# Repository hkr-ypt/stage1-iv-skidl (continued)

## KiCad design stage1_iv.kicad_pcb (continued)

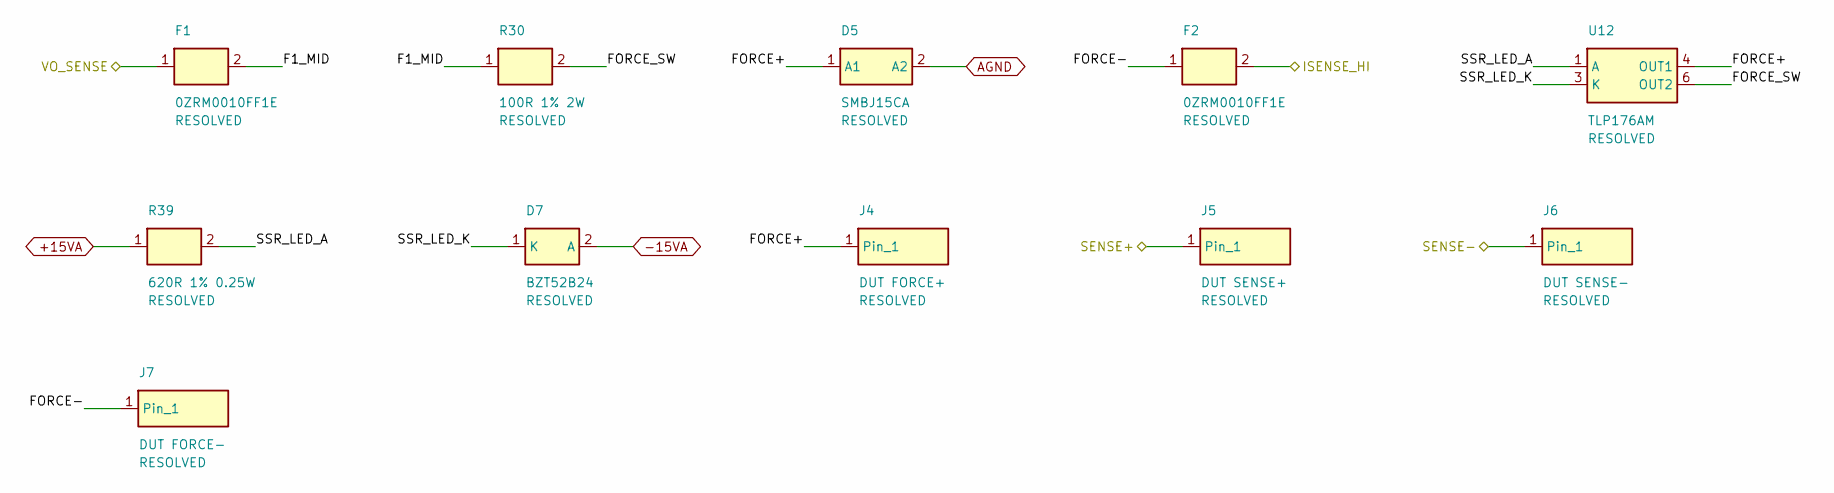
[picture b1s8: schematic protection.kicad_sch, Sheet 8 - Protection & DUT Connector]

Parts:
D5: SMBJ15CA; D_SMB; MPN SMBJ15CA
D7: BZT52B24; D_SOD-123; MPN BZT52B24-E3-08
F1, F2: 0ZRM0010FF1E; Fuse_Bourns_MF-RG300; MPN 0ZRM0010FF1E
J4: DUT FORCE+; Banana_Jack_1Pin; MPN panel-mount-banana-4mm
J5: DUT SENSE+; Banana_Jack_1Pin; MPN panel-mount-banana-4mm
J6: DUT SENSE-; Banana_Jack_1Pin; MPN panel-mount-banana-4mm
J7: DUT FORCE-; Banana_Jack_1Pin; MPN panel-mount-banana-4mm
R30: 100R 1% 2W; R_Axial_DIN0411_L9.9mm_D3.6mm_P12.70mm_Horizontal; MPN PR02000201000FA100
R39: 620R 1% 0.25W; R_1206_3216Metric; MPN generic
U12: TLP176AM; Toshiba_SOIC-4-6_4.4x3.6mm_P1.27mm; MPN TLP176AM(TPL,E

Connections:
+15VA: R39.1; also elsewhere on the board
-15VA: D7.2 (A); also elsewhere on the board
/ISENSE_HI: F2.2; also elsewhere on the board
/SENSE+: J5.1; also elsewhere on the board
/SENSE-: J6.1; also elsewhere on the board
/VO_SENSE: F1.1; also elsewhere on the board
/protection/F1_MID: F1.2, R30.1
/protection/FORCE+: D5.1 (A1), J4.1, U12.4 (OUT1)
/protection/FORCE-: F2.1, J7.1
/protection/FORCE_SW: R30.2, U12.6 (OUT2)
/protection/SSR_LED_A: R39.2, U12.1 (A)
/protection/SSR_LED_K: D7.1 (K), U12.3 (K)
AGND: D5.2 (A2); also elsewhere on the board

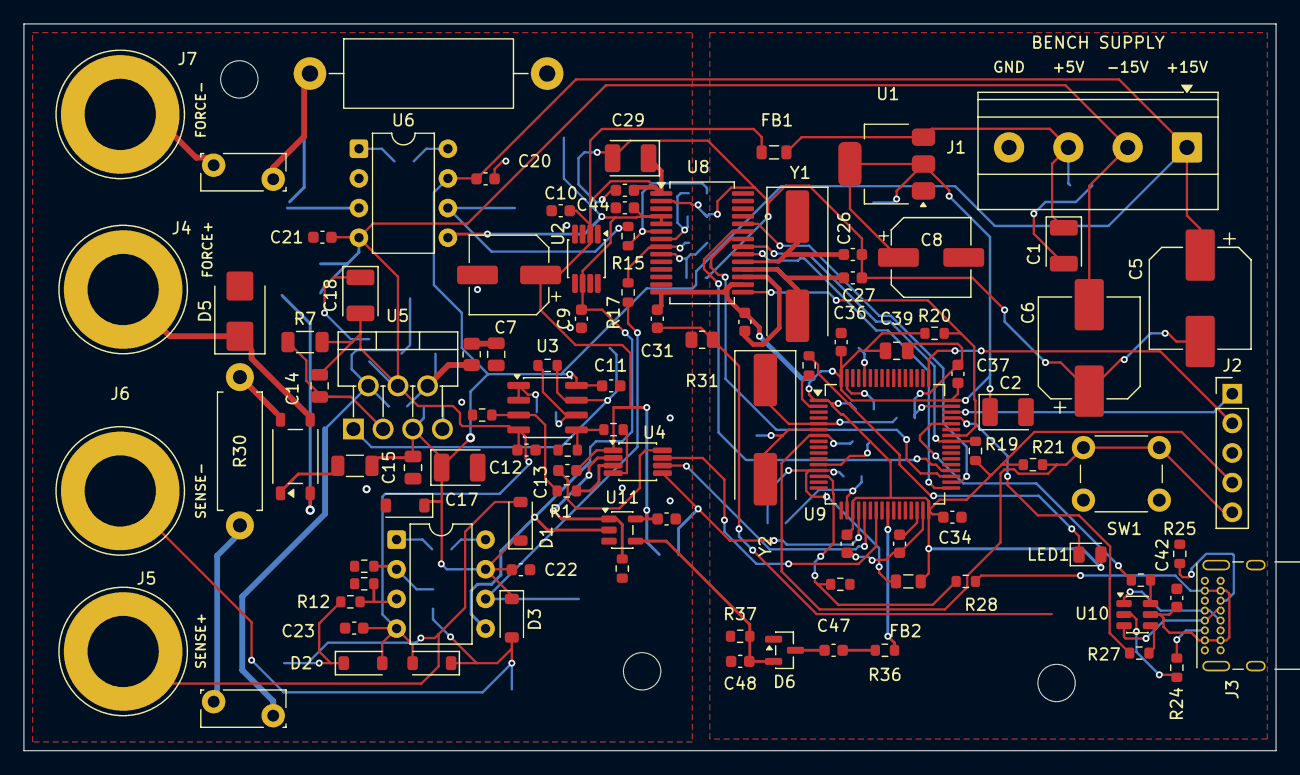
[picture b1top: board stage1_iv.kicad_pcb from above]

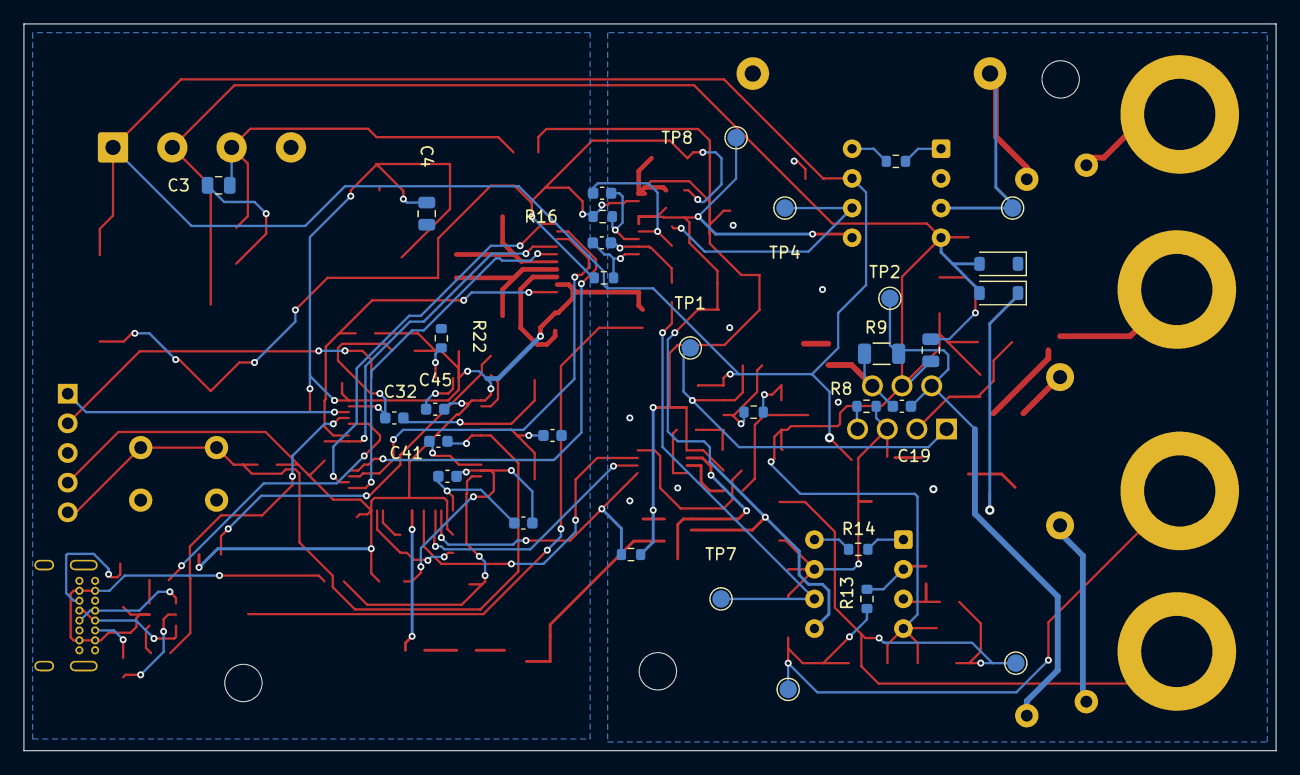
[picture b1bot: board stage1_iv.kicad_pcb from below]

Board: 2 copper layers, 107.2 x 62.2 mm, 135 parts (32 on the bottom side), 77 nets.

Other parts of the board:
H1, H2, H3: MountingHole_3.2mm_M3; MountingHole_3.2mm_M3_Isolated

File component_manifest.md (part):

# Component Manifest — Stage 1 I–V Characterization System

Total components: **141** — 132 on the board (131 fitted, 1 DNP footprints) and 9 schematic-only PWR_FLAG symbols.

**Before buying.** A line whose MPN is `generic` is not a free choice. The tolerance, dielectric, power and voltage ratings that the values below do not carry, and the parts that must be bought by exact code, are in `docs/final_audit.md` §6 ("Buying the parts") and `docs/bringup_checklist.md` §1.

| Ref | Value | MPN | KiCad Library | Footprint | Sheet | Fit | Status |
|-----|-------|-----|---------------|-----------|-------|-----|--------|
| #FLG1 | +15VA | n/a | power:PWR_FLAG |  | 1 Power | virtual | OK — pin numbers read from power.kicad_sym:9842 |
| #FLG2 | -15VA | n/a | power:PWR_FLAG |  | 1 Power | virtual | OK — pin numbers read from power.kicad_sym:9842 |
| #FLG3 | +5V_RAW | n/a | power:PWR_FLAG |  | 1 Power | virtual | OK — pin numbers read from power.kicad_sym:9842 |
| #FLG4 | DGND | n/a | power:PWR_FLAG |  | 1 Power | virtual | OK — pin numbers read from power.kicad_sym:9842 |
| #FLG5 | +5VA | n/a | power:PWR_FLAG |  | 1 Power | virtual | OK — pin numbers read from power.kicad_sym:9842 |
| #FLG6 | AGND | n/a | power:PWR_FLAG |  | 1 Power | virtual | OK — pin numbers read from power.kicad_sym:9842 |
| #FLG7 | VBUS | n/a | power:PWR_FLAG |  | 2 MCU | virtual | OK — pin numbers read from power.kicad_sym:9842 |
| #FLG8 | VDDA | n/a | power:PWR_FLAG |  | 2 MCU | virtual | OK — pin numbers read from power.kicad_sym:9842 |
| #FLG9 | DAC_VREF | n/a | power:PWR_FLAG |  | 3 DAC/Sweep | virtual | OK — pin numbers read from power.kicad_sym:9842 |
| C1 | 10uF/25V | generic | Device:C_Polarized | Capacitor_Tantalum_SMD:CP_EIA-3528-21_Kemet-B | 1 Power | fit | OK — pin numbers read from Device.kicad_sym:5140 |
| C2 | 10uF/16V | generic | Device:C_Polarized | Capacitor_Tantalum_SMD:CP_EIA-3528-21_Kemet-B | 1 Power | fit | OK — pin numbers read from Device.kicad_sym:5140 |
| C3 | 100nF | generic | Device:C | Capacitor_SMD:C_0805_2012Metric | 1 Power | fit | OK — pin numbers read from Device.kicad_sym:1761 |
| C4 | 100nF | generic | Device:C | Capacitor_SMD:C_0805_2012Metric | 1 Power | fit | OK — pin numbers read from Device.kicad_sym:1761 |
| C5 | 100uF/25V | generic | Device:C_Polarized | Capacitor_SMD:CP_Elec_8x10.5 | 1 Power | fit | OK — pin numbers read from Device.kicad_sym:5140 |
| C6 | 100uF/25V | generic | Device:C_Polarized | Capacitor_SMD:CP_Elec_8x10.5 | 1 Power | fit | OK — pin numbers read from Device.kicad_sym:5140 |
| C7 | 100uF/16V | generic | Device:C_Polarized | Capacitor_SMD:CP_Elec_6.3x7.7 | 1 Power | fit | OK — pin numbers read from Device.kicad_sym:5140 |
| C8 | 100uF/10V | generic | Device:C_Polarized | Capacitor_SMD:CP_Elec_6.3x5.4 | 1 Power | fit | OK — pin numbers read from Device.kicad_sym:5140 |
| C9 | 4.7uF 10V X7R | generic | Device:C | Capacitor_SMD:C_0603_1608Metric | 1 Power | fit | OK — pin numbers read from Device.kicad_sym:1761 |
| C10 | 100nF | generic | Device:C | Capacitor_SMD:C_0603_1608Metric | 1 Power | fit | OK — pin numbers read from Device.kicad_sym:1761 |
| C11 | 100nF 50V X7R | generic | Device:C | Capacitor_SMD:C_0603_1608Metric | 3 DAC/Sweep | fit | OK — pin numbers read from Device.kicad_sym:1761 |
| C12 | 100nF 50V X7R | generic | Device:C | Capacitor_SMD:C_0603_1608Metric | 3 DAC/Sweep | fit | OK — pin numbers read from Device.kicad_sym:1761 |
| C13 | 100nF | generic | Device:C | Capacitor_SMD:C_0603_1608Metric | 3 DAC/Sweep | fit | OK — pin numbers read from Device.kicad_sym:1761 |
| C14 | 0.01uF | generic | Device:C | Capacitor_SMD:C_0805_2012Metric | 4 Power Buffer | fit | OK — pin numbers read from Device.kicad_sym:1761 |
| C15 | 100nF 50V X7R | generic | Device:C | Capacitor_SMD:C_0805_2012Metric | 4 Power Buffer | fit | OK — pin numbers read from Device.kicad_sym:1761 |
| C16 | 100nF 50V X7R | generic | Device:C | Capacitor_SMD:C_0805_2012Metric | 4 Power Buffer | fit | OK — pin numbers read from Device.kicad_sym:1761 |
| C17 | 10uF/35V | TCJB106M035R0200E | Device:C_Polarized | Capacitor_Tantalum_SMD:CP_EIA-3528-21_Kemet-B | 4 Power Buffer | fit | OK — pin numbers read from Device.kicad_sym:5140 |
| C18 | 10uF/35V | TCJB106M035R0200E | Device:C_Polarized | Capacitor_Tantalum_SMD:CP_EIA-3528-21_Kemet-B | 4 Power Buffer | fit | OK — pin numbers read from Device.kicad_sym:5140 |
| C19 | 100pF | generic | Device:C | Capacitor_SMD:C_0603_1608Metric | 4 Power Buffer | fit | OK — pin numbers read from Device.kicad_sym:1761 |
| C20 | 100nF 50V X7R | generic | Device:C | Capacitor_SMD:C_0603_1608Metric | 5 Current Sense | fit | OK — pin numbers read from Device.kicad_sym:1761 |
| C21 | 100nF 50V X7R | generic | Device:C | Capacitor_SMD:C_0603_1608Metric | 5 Current Sense | fit | OK — pin numbers read from Device.kicad_sym:1761 |
| C22 | 100nF 50V X7R | generic | Device:C | Capacitor_SMD:C_0603_1608Metric | 6 Voltage Sense | fit | OK — pin numbers read from Device.kicad_sym:1761 |
| C23 | 100nF 50V X7R | generic | Device:C | Capacitor_SMD:C_0603_1608Metric | 6 Voltage Sense | fit | OK — pin numbers read from Device.kicad_sym:1761 |
| C24 | 1nF | generic | Device:C | Capacitor_SMD:C_0603_1608Metric | 7 ADC | fit | OK — pin numbers read from Device.kicad_sym:1761 |
| C25 | 1nF | generic | Device:C | Capacitor_SMD:C_0603_1608Metric | 7 ADC | fit | OK — pin numbers read from Device.kicad_sym:1761 |
| C26 | 18pF | generic | Device:C | Capacitor_SMD:C_0603_1608Metric | 7 ADC | fit | OK — pin numbers read from Device.kicad_sym:1761 |
| C27 | 18pF | generic | Device:C | Capacitor_SMD:C_0603_1608Metric | 7 ADC | fit | OK — pin numbers read from Device.kicad_sym:1761 |
| C28 | 100nF | generic | Device:C | Capacitor_SMD:C_0603_1608Metric | 7 ADC | fit | OK — pin numbers read from Device.kicad_sym:1761 |
| C29 | 10uF/16V | generic | Device:C_Polarized | Capacitor_Tantalum_SMD:CP_EIA-3528-21_Kemet-B | 7 ADC | fit | OK — pin numbers read from Device.kicad_sym:5140 |
| C30 | 100nF | generic | Device:C | Capacitor_SMD:C_0603_1608Metric | 7 ADC | fit | OK — pin numbers read from Device.kicad_sym:1761 |
| C31 | 100nF | generic | Device:C | Capacitor_SMD:C_0603_1608Metric | 7 ADC | fit | OK — pin numbers read from Device.kicad_sym:1761 |
| C32 | 20pF | generic | Device:C | Capacitor_SMD:C_0603_1608Metric | 2 MCU | fit | OK — pin numbers read from Device.kicad_sym:1761 |
| C33 | 20pF | generic | Device:C | Capacitor_SMD:C_0603_1608Metric | 2 MCU | fit | OK — pin numbers read from Device.kicad_sym:1761 |
| C34 | 100nF | generic | Device:C | Capacitor_SMD:C_0603_1608Metric | 2 MCU | fit | OK — pin numbers read from Device.kicad_sym:1761 |
| C35 | 100nF | generic | Device:C | Capacitor_SMD:C_0603_1608Metric | 2 MCU | fit | OK — pin numbers read from Device.kicad_sym:1761 |
| C36 | 100nF | generic | Device:C | Capacitor_SMD:C_0603_1608Metric | 2 MCU | fit | OK — pin numbers read from Device.kicad_sym:1761 |
| C37 | 100nF | generic | Device:C | Capacitor_SMD:C_0603_1608Metric | 2 MCU | fit | OK — pin numbers read from Device.kicad_sym:1761 |
| C38 | 100nF | generic | Device:C | Capacitor_SMD:C_0603_1608Metric | 2 MCU | fit | OK — pin numbers read from Device.kicad_sym:1761 |
| C39 | 4.7uF | generic | Device:C | Capacitor_SMD:C_0805_2012Metric | 2 MCU | fit | OK — pin numbers read from Device.kicad_sym:1761 |
| C40 | 1uF | generic | Device:C | Capacitor_SMD:C_0603_1608Metric | 2 MCU | fit | OK — pin numbers read from Device.kicad_sym:1761 |
| C41 | 100nF | generic | Device:C | Capacitor_SMD:C_0603_1608Metric | 2 MCU | fit | OK — pin numbers read from Device.kicad_sym:1761 |
| C42 | 100nF | generic | Device:C | Capacitor_SMD:C_0603_1608Metric | 2 MCU | fit | OK — pin numbers read from Device.kicad_sym:1761 |
| C43 | 4.7uF 10V X5R | generic | Device:C | Capacitor_SMD:C_0603_1608Metric | 2 MCU | fit | OK — pin numbers read from Device.kicad_sym:1761 |
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
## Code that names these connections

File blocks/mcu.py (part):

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(USB-C + ESD array), reset and boot circuitry, and status LED.

Two PHYSICALLY SEPARATE SPI buses (spec §C.1):
    SPI1 (PA5/PA7/PA4)  -> DAC  (write-only)
    SPI2 (PB13/15/14/12)-> ADC  (bidirectional)

NOTE — C43 (VCAP1 decoupling) is added here for electrical completeness: the
STM32F4 internal LDO requires it and it was absent from the source component
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
SAFE-STATE HEARTBEAT (audit F2)
-------------------------------
PC5 -> R36 -> C47 -> D6 (BAT54S) -> DAC_ARM, held by C48 and bled by R37: a
diode charge pump that turns a SOFTWARE-toggled square wave into the enable
of the DAC reference gate U11 (Sheet 3). Nothing but edges reaches DAC_ARM —
there is no DC path from any rail — so a reset (pins float), a debugger halt,
a crash, a pin stuck high or low, or an unpowered MCU all drop DAC_ARM below
U11's VIL within ~52 ms and the sweep output to zero. R36 limits the PC5
edge current to 3.3 mA. Component values and their simulated margins are in
blocks/dac_sweep.py; the firmware contract is docs/firmware_handoff.md.

STATUS LED: SUNK BY PC13, NOT SOURCED
-------------------------------------
PC13..PC15 sit behind the backup-domain power switch; DS10314 says they can
sink only 3 mA and "must not be used as a current source (e.g. to drive an
LED)". LED1 is therefore lit by PC13 pulling LOW: +3V3D -> LED1 -> R23 ->
PC13. R23 = 1 k gives ~1 mA (green Vf ~2 V): visible, and a third of the
3 mA limit. (It was 330 R, sourced from PC13.)
"""

from libraries.custom_symbols import (
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    n.DGND += C43[2]

    # ---- HSE crystal ----
    osc_in = Net("OSC_IN"); osc_in += U9["PH0"], Y2[1], C32[1]
    osc_out = Net("OSC_OUT"); osc_out += U9["PH1"], Y2[2], C33[1]
    n.DGND += C32[2], C33[2]

    # ---- reset / boot ----
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    n.DGND += R22[2]

    # ---- SWD ----
    n.SWDIO += U9["PA13"], J2["Pin_1"]
    n.SWCLK += U9["PA14"], J2["Pin_2"]
    n.DGND += J2["Pin_3"]

    # ---- SPI1 (DAC, write-only) ----
    n.SCK1 += U9["PA5"]
    n.MOSI1 += U9["PA7"]
    n.CS_DAC += U9["PA4"]

    # ---- SPI2 (ADC, bidirectional) ----
    n.SCK2 += U9["PB13"]
    n.MOSI2 += U9["PB15"]
    n.MISO2 += U9["PB14"]
    n.CS_ADC += U9["PB12"]
    n.DRDY += U9["PA8"]
    n.RESET_ADC += U9["PA9"]

    # ---- USB OTG-FS with series R + ESD array ----
    n.USB_DM += U9["PA11"], R26[1]
    esd_dm = Net("USB_DM_ESD"); esd_dm += R26[2], U10["IO1b"]
    conn_dm = Net("USB_DM_CONN"); conn_dm += U10["IO1"], J3["DM"]

    n.USB_DP += U9["PA12"], R27[1]
    esd_dp = Net("USB_DP_ESD"); esd_dp += R27[2], U10["IO2b"]
    conn_dp = Net("USB_DP_CONN"); conn_dp += U10["IO2"], J3["DP"]

    # J3["VBUS"] is all four VBUS pads (A4, A9, B4, B9) of the receptacle.
    n.VBUS += J3["VBUS"], U10["VBUS"], R28[1], C42[1]
    n.DGND += C42[2], U10["GND"]
    n.VBUS_SENSE += R28[2], R29[1], U9["PA0"]
    n.DGND += R29[2]

    # USB-C CC pull-downs (UFP identification)
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
    # USB-C shield (pad S1, four physical shell tabs): tied DIRECTLY to DGND.
    # This is a deliberate choice, not an omission. The board is powered from
    # the bench supply at J1 (VBUS only feeds the PA0 sense divider and U10's
    # clamp) and is single-enclosure, so there is no chassis/signal-ground potential
    # difference for an RC or ferrite path to manage; a direct tie gives the
    # lowest-impedance return for cable-shield ESD and CM currents and keeps
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    # SBU1/SBU2 (pads A8/B8) carry no sideband signalling in this design.
    nc_named(J3, "SBU1", "SBU2")

    # ---- status LED: sunk by PC13 (see header) ----
    n.LED_STATUS += U9["PC13"], R23[1]
    led_k = Net("LED_K"); led_k += R23[2], LED1["K"]
    n.P3V3D += LED1["A"]

    # ---- safe-state heartbeat: PC5 -> charge pump -> DAC_ARM (Sheet 3) ----
    # (The passives are wired pad 2 = signal side, pad 1 = the next node
    # west, so that laid out at 0 degrees the chain runs east -> west from
    # the heartbeat via to the moat: the board chose the pad numbers.)
    hb = Net("SAFE_HB"); hb += U9["PC5"], R36[2]
    hb_r = Net("SAFE_HB_R"); hb_r += R36[1], C47[2]
    hb_ac = Net("SAFE_HB_AC"); hb_ac += C47[1], D6["COM"]
    n.DGND += D6["A"]
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        "PC14", "PC15",                                  # LSE oscillator (unused)
        "PC0", "PC1", "PC2", "PC3",                      # port C low
        "PA1", "PA2", "PA3", "PA6",                      # port A spares
        "PC4",                                           # (PC5: heartbeat)
        "PB0", "PB1", "PB2", "PB10",                     # port B spares
        "PC6", "PC7", "PC8", "PC9",
        "PA10",                                          # USB_ID (device only)
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
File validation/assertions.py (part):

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
These encode the design intent that ERC cannot: topology, reference sharing,
Kelvin independence, bus separation, star grounding, the bipolar
measurement zero (both INA128 REF pins and the ADC's AINCOM on VREF_2V5), and
the audit-F2 safe state (the sweep midpoint from DAC channel B, the DAC
reference gate, and the rule that only a toggling heartbeat can arm it).
Each check works on the actual net membership of the built circuit and
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    """The DAC and the ADC are referenced to the same REF5025 output.

    The DAC's reference reaches VREF_2V5 THROUGH the gate U11 (audit F2):
    U11.S on VREF_2V5, U11.D on the DAC's VREF pin. A U4.VREF wired straight
    to VREF_2V5 would bypass the reset-safe gate, so that is a failure too.
    """
    dac_ref = _net_of(_pin(circuit, "U4", "VREF"))
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    c1 = _has(n.VO_SENSE, "U5") and _has(n.VO_SENSE, "R9") and _has(n.VO_SENSE, "F1")
    c2 = _has(n.F1_MID, "F1") and _has(n.F1_MID, "R30")
    sw = None
    r30 = next((p for p in n.F1_MID.get_pins() if p.part.ref == "R30"), None)
    if r30 is not None:
        sw = _net_of(_two_pin_far(r30.part, r30))
    c3 = (sw is not None and sorted(_refs_on(sw)) == ["R30", "U12"]
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    fm = sorted(_refs_on(n.FORCE_MINUS))
    if fm != ["F2", "J7"]:
        problems.append(f"FORCE- holds {fm}, not exactly J7 and F2")
    pins = list(n.ISENSE_HI.get_pins())
    hi = sorted(p.part.ref for p in pins)
    if hi != ["F2", "R10", "TP3", "U6"]:
        problems.append(f"ISENSE_HI holds {hi}; expected exactly one pin "
                        f"each of F2, R10, TP3 and U6")
    if not _has(n.ISENSE_HI, "U6", "+IN"):
        problems.append("U6.+IN is not on ISENSE_HI")
    r10 = next((p for p in pins if p.part.ref == "R10"), None)
    if r10 is None or _two_pin_far(r10.part, r10) not in n.AGND.get_pins():
        problems.append("R10 does not run from ISENSE_HI to AGND")
    if not _has(n.AGND, "U6", "-IN"):
        problems.append("U6.-IN is not on AGND (the shunt's low side)")
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    # Kelvin sense nets must share NO pins with the force nets.
    sp = _pin_ids(n.SENSE_PLUS) & _pin_ids(n.FORCE_PLUS)
    sm = (_pin_ids(n.SENSE_MINUS) & _pin_ids(n.FORCE_MINUS)) | \
        (_pin_ids(n.SENSE_MINUS) & _pin_ids(n.ISENSE_HI))
    # And the voltage-sense amp (U7) must reach the SENSE nets, not the FORCE nets.
    u7_on_sense = _has(n.SENSE_PLUS, "U7") is False  # U7 sits behind R12/R13
    force_free = (not _refs_on(n.SENSE_PLUS) & {"R10"}
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

def a_spi_buses_separate(n):
    shared = _pin_ids(n.SCK1) & _pin_ids(n.SCK2)
    ok = not shared
    return ("SPI1 and SPI2 are physically separate buses", ok,
            f"pins common to SCK1 and SCK2 = {shared or 'none'}")


def a_star_ground(n):
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    dgnd_refs = _refs_on(n.DGND)
    both = agnd_refs & dgnd_refs           # parts touching both planes
    # A part legitimately straddles both planes only if it is a multi-pin IC
    # (separate AGND/DGND pins, e.g. ADS1256). An accidental SECOND star join
    # would be a 2-terminal R/C/L shorting the planes. Flag any such extra part.
    extra_bridges = set()
    for ref in both:
        if ref == "R31":
            continue
        # find the part
        part = next(p.part for p in n.AGND.get_pins() if p.part.ref == ref)
        if part.ref[0] in ("R", "C", "F", "L") and len(part.pins) == 2:
            extra_bridges.add(ref)
    ok = bridge and not extra_bridges
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    current or voltage fell below that floor. REF on VREF_2V5 moves zero to
    2.500 V, and AINCOM on the SAME net makes the conversion AIN - AINCOM,
    in which the 2.5 V cancels and the sign survives. All three have to move
    together: any one left on AGND puts a 2.5 V offset (or the old clipping)
    back into a channel.
    """
    want = [("U6", "REF"), ("U7", "REF"), ("U8", "AINCOM")]
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
    R1 from U4.VOUTB to U3A's input, R2 from there to AGND: both channels
    then power up at zero scale together and V_SWEEP starts at 0 V. Any R1/R2
    pin on VREF_2V5 brings back the -10 V power-up output.
    """
    problems = []
    vb = _net_of(_pin(circuit, "U4", "VOUTB"))
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

def a_dac_reference_gate(n, circuit):
    """U4's VREF pin is VREF_2V5 only through U11, and 0 V otherwise (F2)."""
    problems = []
    dac_ref = _net_of(_pin(circuit, "U4", "VREF"))
    if dac_ref is None or not _has(dac_ref, "U11", "D"):
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

def a_arm_needs_a_heartbeat(n, circuit):
    """Nothing but a toggling PC5 can raise DAC_ARM (F2's fail-safe property).

    DAC_ARM may hold only: U11.SEL (an input), D6.K (the pump rectifier),
    capacitors, and resistors whose other end is a ground. D6's other diode
    clamps to DGND; the pump's AC node is fed only through C47; C47 is fed
    only through R36 from PC5. A resistor from DAC_ARM to any rail, or a DC
    path past C47, would let a static level (a reset, a halt, a stuck pin)
    hold the output armed — which is exactly what this design must not do.
    """
    problems = []
    grounds = (n.AGND, n.DGND)
    for p in n.DAC_ARM.get_pins():
        ref, name = p.part.ref, p.name
        if (ref, name) in (("U11", "SEL"), ("D6", "K")):
            continue
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    if ac_refs != {"D6", "C47"}:
        problems.append(f"pump AC node holds {sorted(ac_refs)}, expected "
                        f"D6 and C47 only")
    hb = _net_of(_pin(circuit, "U9", "PC5"))
    if hb is None or _refs_on(hb) != {"U9", "R36"}:
        problems.append(f"PC5 does not drive the pump through R36 alone "
                        f"({sorted(_refs_on(hb)) if hb else None})")
    return ("DAC_ARM: only a toggling PC5 can arm it (AC-coupled pump, no DC "
            "path from any rail)", not problems,
            "; ".join(problems) or
            f"DAC_ARM: {sorted(_refs_on(n.DAC_ARM))}")
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def a_cs_dac_pulled_up(n, circuit):
    """SYNC idles high while the MCU's pins float (reset, boot)."""
    ups = []
    for p in n.CS_DAC.get_pins():
        if p.part.ref[0] == "R" and len(p.part.pins) == 2:
            far = _two_pin_far(p.part, p)
            rails = [x.name for x in far.get_nets()]
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
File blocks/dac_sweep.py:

"""
dac_sweep.py — SHEET 3: DAC & Sweep Level-Shift
===============================================

DAC8552 (16-bit, both channels used) drives a precision level-shift stage built
from the dual OPA2277:

    U3A : unity-gain buffer of the R1/R2 midpoint (low-Z VREF_HALF)
    U3B : 4-resistor difference amplifier

        VREF_HALF = V_DACB * R2/(R1 + R2) = V_DACB / 2
        V_SWEEP   = (R4/R3) * (V_DAC - VREF_HALF)
                  = 8.0321 * (V_A - V_B/2)          V_A, V_B = DAC A/B outputs

Firmware writes channel B to full scale once per boot (V_B = 2.500 V, so
VREF_HALF = 1.250 V) and sweeps channel A over 0..2.500 V; then
(V_A - 1.25 V) spans +/-1.250 V and the gain 20.0k/2.49k = 8.0321 puts V_SWEEP
at +/-10.040 V (spec §C.5).

WHY THE MIDPOINT COMES FROM CHANNEL B, NOT FROM VREF_2V5 (audit F2)
-------------------------------------------------------------------
With R1 on VREF_2V5, VREF_HALF was a fixed 1.25 V and the DAC's guaranteed
power-on state (zero scale, SLAS430A) meant V_SWEEP = 8.03 * (0 - 1.25 V)
= -10.04 V: full negative output into the DUT from power-up until firmware
first wrote the DAC. With the midpoint on VOUTB, both channels power up at
zero scale and V_SWEEP = 8.03 * (0 - 0) = 0, residual offsets only.

    Bound            Mechanism                              Class
    -10.04 V min     V_A >= 0, V_B <= VREF: no code can     hardware
                     push V_SWEEP lower
    +10.04 V max     ONLY while channel B = full scale.     FIRMWARE CONTRACT
                     B below full scale raises the ceiling:
                     B = 0, A = FS commands +20.1 V. U3B is
                     guaranteed to swing to at least
                     (V+) - 1.2 V = +13.8 V (SBOS079C), so
                     the real ceiling is 13.8 V..the +15 V
                     rail, past U5's specified input range
                     ((V+) - 3 V = +12 V, SBOS056F).

The firmware requirements this creates are listed in docs/firmware_handoff.md
and are not hardware protection.

THE DAC REFERENCE GATE (U11) — RESET, HALT AND CRASH
----------------------------------------------------
The DAC8552 has no reset or clear pin and HOLDS its codes through an MCU reset,
a debugger halt or a firmware crash: the zero-scale power-on state is
guaranteed only at DAC power-up. So the hardware forces the output to zero by
another route. The DAC8552 is a resistor-string DAC whose outputs are
VREF * code / 65536 for both channels (SLAS430A, "Theory of operation"), and
both channels share one VREF pin. U11 (TMUX1101, SPST) connects that pin to
VREF_2V5 only while DAC_ARM is high; otherwise the pin is open and R35 pulls
it to AGND. With VREF = 0 both outputs are 0 V WHATEVER CODES THE DAC HOLDS,
so V_SWEEP = 8.03 * (0 - 0/2) = 0. Because the midpoint is ratiometric to the
same pin, the zero holds with no matching requirement.

DAC_ARM is not a GPIO level. It is the rectified output of a diode charge
pump (Sheet 2, D6/C47/C48/R37) fed by a SOFTWARE-toggled heartbeat on PC5:

    * no DC path from any supply to DAC_ARM exists; only edges transfer charge
    * a single GPIO transition reaches ~0.53 V, below U11's VIL (0.87 V)
    * >= 1 kHz heartbeat: DAC_ARM 2.4 V nominal, 1.9 V worst case
      (VOH 3.0 V, diodes 0.4 V, 10 uA leakage) vs VIH 1.49 V
    * heartbeat stops (reset, halt, crash, a stuck pin, MCU unpowered):
      DAC_ARM < 0.87 V, U11 off, within ~52 ms (C48 * R37 = 47 ms)

PC5 has no timer or peripheral output function on the STM32F411 (only
EVENTOUT), so no peripheral can keep toggling it once the CPU stops. The
pump's numbers are from a transient simulation of this circuit; the bring-up
plan measures them (docs/bringup_checklist.md).

U11's on-resistance (1.8 ohm typ, 4.9 ohm max at 125 C, SCDS410D) in series with
the DAC's 62 kohm reference input scales both channels by the same 30..80 ppm:
the A/B ratio and therefore
the zero point are unaffected, and the full-scale error calibrates out with
the rest of the source gain (it is a setpoint, not a measurement — V and I are
measured independently by the ADC).

R4 = R6 = 20.0k BRACKETS the +/-10 V target rather than landing on it: an exact
+/-10.000 V needs 8.000 * 2.49k = 19.92k, which is in no standard series, and
the nearest value below it (19.8k, E192) reaches only +/-9.94 V and so could
never get to 10 V at all. 20.0k is E96 at the same 0.1% grade as R3/R5, and
firmware simply leaves the top 0.40% of the DAC's codes unused.

U5 headroom for that range (OPA547 on +/-15VA, Sheet 4). U5's feedback is taken
past R9, so its OUT pin must reach V_SWEEP + I*R9: 10.040 + 0.049*10 = 10.53 V
on the nominal 49 mA plateau, 10.95 V at the 91.3 mA passive bound, and its
"+IN" sits at V_SWEEP = 10.04 V. SBOS056F guarantees, at I_O = 0.1 A (more
than any current this stage can pass in normal operation):

    output swing    (V+)-1.8 = +13.2 V  vs +10.95 V needed  ->  2.25 V spare
                    (V-)+1.2 = -13.8 V  vs -10.95 V needed  ->  2.85 V spare
    input com-mode  (V+)-3.0 = +12.0 V  vs +10.04 V on +IN  ->  1.96 V spare

so the rails deliver +/-10.04 V with margin. D5 (SMBJ15CA, 15 V standoff,
Sheet 8) still stands off above it and does not clip it.

C11/C12 sit on the +/-15 V rails and are rated 50 V X7R (audit: >= 25 V).
"""

from libraries.custom_symbols import (
    DAC8552, OPA2277, TMUX1101, R, C, TestPoint, PWR_FLAG,
)
from skidl import Net


def create_dac_block(n):
    U4 = DAC8552()(ref="U4", tag="U4", value="DAC8552IDGKR")
    C13 = C()(ref="C13", tag="C13", value="100nF")
    U3 = OPA2277()(ref="U3", tag="U3", value="OPA2277UA")
    C11 = C()(ref="C11", tag="C11", value="100nF 50V X7R")
    C12 = C()(ref="C12", tag="C12", value="100nF 50V X7R")
    R1 = R()(ref="R1", tag="R1", value="10.0k 0.1%")
    R2 = R()(ref="R2", tag="R2", value="10.0k 0.1%")
    R3 = R()(ref="R3", tag="R3", value="2.49k 0.1%")
    R5 = R()(ref="R5", tag="R5", value="2.49k 0.1%")
    R4 = R()(ref="R4", tag="R4", value="20.0k 0.1%")
    R6 = R()(ref="R6", tag="R6", value="20.0k 0.1%")
    TP1 = TestPoint()(ref="TP1", tag="TP1", value="V_SWEEP")
    U11 = TMUX1101()(ref="U11", tag="U11", value="TMUX1101DBVR")
    C46 = C()(ref="C46", tag="C46", value="100nF")
    R35 = R()(ref="R35", tag="R35", value="1M")
    # CS_DAC (SYNC) pull-up, at the DAC end: holds SYNC high while the MCU's
    # pins float (reset, boot, unpowered MCU), so no frame can be clocked in
    # during U11's ~50 ms disarm. To +5VA, the DAC's own rail, because only
    # that rail is on this side of the AGND/DGND split here; 100 k keeps the
    # current into PA4 when it is an input or driven to 3.3 V at <= 17 uA
    # (PA4 is an FT pin, DS10314 Table 8: 5 V tolerant, nothing is injected). SYNC's
    # VINH is 2.4 V, so the MCU's 3.3 V drive still reads high.
    R34 = R()(ref="R34", tag="R34", value="100k")

    # ---- DAC power + SPI1 (write-only) ----
    n.P5VA += U4["VDD"], C13[1]
    n.AGND += C13[2], U4["GND"]
    n.CS_DAC += U4["SYNC"], R34[2]
    n.P5VA += R34[1]
    n.SCK1 += U4["SCLK"]
    n.MOSI1 += U4["DIN"]
    n.V_DAC += U4["VOUTA"], R3[1]
    v_dacb = Net("V_DACB"); v_dacb += U4["VOUTB"], R1[1]   # midpoint source

    # ---- DAC reference gate: VREF reaches the DAC only while armed ----
    dac_vref = Net("DAC_VREF"); dac_vref += U4["VREF"], U11["D"], R35[1]
    # U4's VREF pin is power_in. Its source is the REF5025 THROUGH U11, whose
    # D/S pins are passive, so ERC sees no driver on DAC_VREF — the same
    # situation as +5VA after FB1 and VDDA after FB2, and stated the same way.
    FLG9 = PWR_FLAG()(ref="#FLG9", tag="FLG9", value="DAC_VREF")
    dac_vref += FLG9[1]
    n.VREF_2V5 += U11["S"]
    n.DAC_ARM += U11["SEL"]                # charge-pump output, Sheet 2
    n.AGND += R35[2], U11["GND"]
    n.P5VA += U11["VDD"], C46[1]
    n.AGND += C46[2]

    # ---- V_DACB/2 divider + U3A unity buffer ----
    vref_half_raw = Net("VREF_HALF_RAW")
    vref_half_raw += R1[2], R2[1], U3["+INA"]
    n.AGND += R2[2]
    n.VREF_HALF += U3["OUTA"], U3["-INA"], R5[1]   # buffered, low-Z

    # ---- U3B 4-resistor difference amplifier ----
    node_p = Net("DIFF_P"); node_p += R3[2], R4[1], U3["+INB"]
    n.AGND += R4[2]
    node_n = Net("DIFF_N"); node_n += R5[2], R6[1], U3["-INB"]
    n.V_SWEEP += U3["OUTB"], R6[2], TP1[1]

    # ---- op-amp supplies ----
    n.P15VA += U3["V+"], C11[1]
    n.AGND += C11[2]
    n.N15VA += U3["V-"], C12[1]
    n.AGND += C12[2]

    return {
        "U4": U4, "C13": C13, "U3": U3, "C11": C11, "C12": C12,
        "R1": R1, "R2": R2, "R3": R3, "R4": R4, "R5": R5, "R6": R6, "TP1": TP1,
        "U11": U11, "C46": C46, "R35": R35, "R34": R34, "FLG9": FLG9,
    }

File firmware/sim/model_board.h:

/*
 * model_board.h — analog behavioural model of the Stage 1 board, from the
 * DAC registers to the ADC input pins (blocks/<name>.py at c4e7592):
 *
 *   PC5 edges -> charge pump DAC_ARM (C48 || R37, tau 47 ms) -> TMUX1101 gate
 *     gate ON at DAC_ARM >= 1.49 V, OFF at <= 0.87 V, holds in between
 *   VREF_DAC = gate ? VREF : 0
 *   V_SWEEP  = 8.0321 * (V_A - V_B/2), V_x = VREF_DAC * code_x / 65536,
 *              clamped to U3B's swing (+-13.8 V)
 *   U5 follower with current limit i_lim (both polarities), only if both
 *     +-15 V rails are up (otherwise U12 is open: no force current)
 *   FORCE+ : R_top = F1 + R30 + U12 ; FORCE- : R_bot = F2 + R10 to AGND
 *   Kelvin attenuators R12/R32, R13/R33 (50.2 k to AGND) on SENSE+/SENSE-
 *   U7: V_SENSE_OUT = VREF + k * (V(SENSE+) - V(SENSE-)) + offset
 *   U6: I_SENSE_OUT = VREF + 24.0056 V/A * I(R10) + offset
 *   ADC pins: AIN0 = I_SENSE_OUT, AIN2 = V_SENSE_OUT, AIN1 = AIN3 = AGND,
 *             AINCOM = VREF
 *
 * The DUT is solved for its operating point by bisection on the DUT voltage
 * (works for any monotonic I(V) DUT). The model is deliberately simple; it
 * exists to exercise the firmware's logic, not to predict analog accuracy.
 */
#ifndef MODEL_BOARD_H
#define MODEL_BOARD_H

#include <stdbool.h>
#include <stdint.h>
#include "model_dac8552.h"

typedef enum {
    DUT_OPEN = 0,
    DUT_RESISTOR,   /* r_ohm                                           */
    DUT_DIODE,      /* is_a, n (ideality), rs_ohm ; anode on FORCE+     */
    DUT_CELL,       /* v_cell, r_ohm (internal) : a battery/PV-like source */
    DUT_CAPACITOR,  /* treated as open at DC (c_f kept for future use)  */
} dut_kind_t;

typedef struct {
    dut_kind_t kind;
    double r_ohm;
    double is_a, n, rs_ohm;
    double v_cell;
    double c_f;
} dut_t;

typedef struct {
    /* configuration (tests may change any of these) */
    double vref;              /* 2.500                                   */
    double sweep_offset_v;    /* residual offset at V_SWEEP              */
    double r_top, r_bot, r_sd;
    double i_lim;             /* current-limit plateau, A                */
    double ina_v_offset_v;    /* U7 output-referred offset               */
    double ina_i_offset_v;    /* U6 output-referred offset               */
    bool   rail_pos, rail_neg;/* +-15 V present                         */
    bool   sense_plus_open, sense_minus_open, force_open;
    double gain_err_v, gain_err_i; /* multiplicative errors (e.g. 0.00168) */
    dut_t  dut;
    /* gate / charge pump state */
    double v_arm;
    bool   gate_on;
    bool   hb_level;
    uint64_t t_last_us;
    uint32_t gate_on_events, gate_off_events;
    /* links */
    dac_model_t *dac;
} board_model_t;

void   board_init(board_model_t *b, dac_model_t *dac);
/* PC5 level at time t (rising edges pump charge). */
void   board_hb(board_model_t *b, bool level, uint64_t t_us);
/* Advance the charge pump decay to time t. */
void   board_advance(board_model_t *b, uint64_t t_us);
double board_vref_dac(const board_model_t *b);
double board_vsweep(const board_model_t *b);
/* Operating point: DUT voltage (V_hi - V_lo), DUT current, shunt current. */
void   board_solve(const board_model_t *b, double *v_hi, double *v_lo,
                   double *i_dut, double *i_shunt, bool *in_limit);
/* adsm_input_fn-compatible callback (ctx = board_model_t *). */
double board_ain(void *ctx, int ain, uint64_t t_us);

#endif /* MODEL_BOARD_H */
